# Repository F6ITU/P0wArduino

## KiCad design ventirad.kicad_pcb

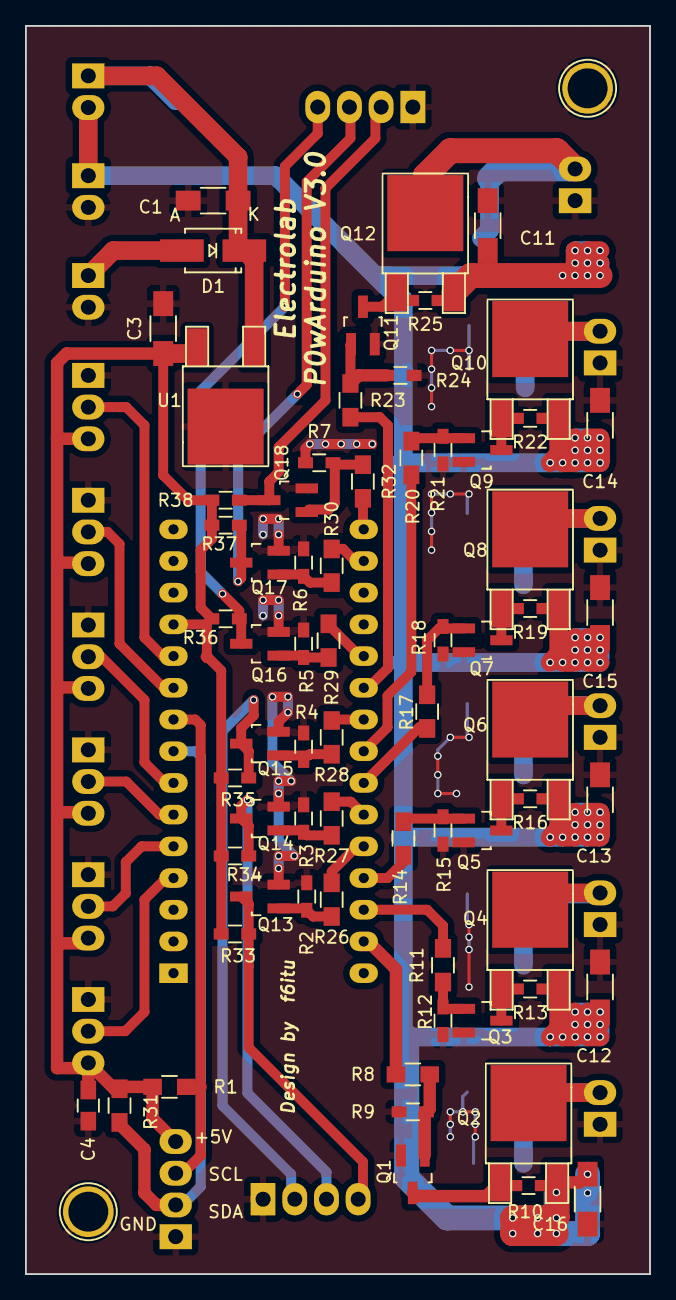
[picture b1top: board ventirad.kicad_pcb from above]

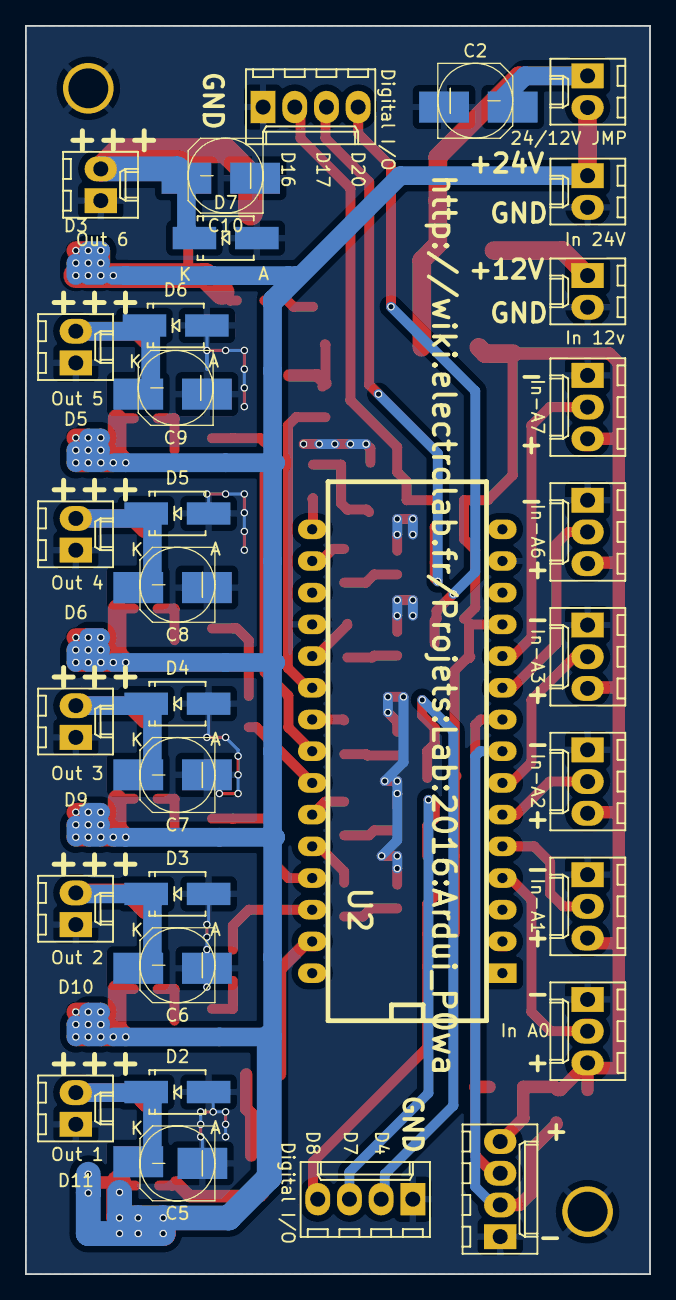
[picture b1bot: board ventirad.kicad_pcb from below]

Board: 2 copper layers, 50.0 x 100.0 mm, 81 parts (14 on the bottom side), 48 nets.

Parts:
C1, C3, C11, C12, C13, C14, C15, C16: 100n; C_1206_HandSoldering
C2: 200u; c_elec_6.3x7.7
C4: 10n; C_0805_HandSoldering
C5, C6, C7, C8, C9, C10: 100u; c_elec_6.3x7.7
D1, D2, D3, D4, D5, D6, D7: SS-26; SMA_Handsoldering
Q1, Q3, Q5, Q7, Q9, Q11, Q13, Q14, Q15, Q16, Q17, Q18: 2N7000; SOT-23_Handsoldering
Q2, Q4, Q6, Q8, Q10, Q12: IRFR9014; TO-252-2Lead
R1, R31: 10k; R_0805_HandSoldering
R2, R3, R4, R5, R6, R7, R9, R10, R12, R13, R15, R16, R18, R19, R21, R22, R24, R25, R33, R34, R35, R36, R37, R38: 10k; R_0603_HandSoldering
R8, R11, R14, R17, R20, R23, R26, R27, R28, R29, R30, R32: 1k; R_0805_HandSoldering
U1: LM7805; TO-252-2Lead
U2: http://wiki.electrolab.fr/Projets:Lab:2016:Ardui_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; arduino_nano

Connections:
+5V: C3.1, C4.1, R1.2, R31.2, R33.1, R34.1, R35.1, R36.1, R37.1, R38.1, U1.3, U2.12
+12V: C1.1, C2.1, D1.1, U1.1
GND: C1.2, C2.2, C3.2, C4.2, C5.2, C6.2, C7.2, C8.2, C9.2, C10.2, C11.1, C12.1, C13.1, C14.1, C15.1, C16.1, D2.2, D3.2, D4.2, D5.2, D6.2, D7.2, Q1.2, Q3.2, Q5.2, Q7.2, Q9.2, Q11.2, Q13.2, Q14.2, Q15.2, Q16.2, Q17.2, Q18.2, R2.2, R3.2, R4.2, R5.2, R6.2, R7.2, R9.2, R12.2, R15.2, R18.2, R21.2, R24.2, U1.2, U2.14, U2.19
unnamed: C5.1, D2.1, Q2.2
unnamed: C6.1, D3.1, Q4.2
unnamed: C7.1, D4.1, Q6.2
unnamed: C8.1, D5.1, Q8.2
unnamed: C9.1, D6.1, Q10.2
unnamed: C10.1, D7.1, Q12.2
unnamed: C11.2, C12.2, C13.2, C14.2, C15.2, C16.2, Q2.3, Q4.3, Q6.3, Q8.3, Q10.3, Q12.3, R10.1, R13.1, R16.1, R19.1, R22.1, R25.1
unnamed: R31.1, U2.8
unnamed: R1.1, U2.9
unnamed: Q15.3, R35.2
unnamed: Q14.3, R34.2
unnamed: Q13.3, R33.2
unnamed: Q18.3, R38.2
unnamed: Q17.3, R37.2
unnamed: Q16.3, R36.2
unnamed: Q1.1, R8.1, R9.1
unnamed: Q1.3, Q2.1, R10.2
unnamed: Q3.1, R11.1, R12.1
unnamed: Q3.3, Q4.1, R13.2
unnamed: Q5.1, R14.1, R15.1
unnamed: Q5.3, Q6.1, R16.2
unnamed: Q7.1, R17.1, R18.1
unnamed: Q7.3, Q8.1, R19.2
unnamed: Q9.1, R20.1, R21.1
unnamed: Q9.3, Q10.1, R22.2
unnamed: Q11.1, R23.1, R24.1
unnamed: Q11.3, Q12.1, R25.2
unnamed: Q13.1, R2.1, R26.1
unnamed: Q14.1, R3.1, R27.1
unnamed: Q15.1, R4.1, R28.1
unnamed: Q16.1, R5.1, R29.1
unnamed: Q17.1, R6.1, R30.1
unnamed: Q18.1, R7.1, R32.1
unnamed: R8.2, U2.29
unnamed: R11.2, U2.28
unnamed: R14.2, U2.27
unnamed: R17.2, U2.24
unnamed: R20.2, U2.23
unnamed: R23.2, U2.21
unnamed: R26.2, U2.26
unnamed: R27.2, U2.25
unnamed: R28.2, U2.22
unnamed: R29.2, U2.20
unnamed: R30.2, U2.17
unnamed: R32.2, U2.16

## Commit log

2016-05-02 Projet Ventirad, projet initial
2017-05-02 version Shielded et empreinte capapol elargies
2018-09-02 lib cleaning, mounting holes
2018-09-02 cleaning rm files
2019-03-15 upgrade to Kicad 5.x
2024-01-02 some file refresh and ibom, kicad 7 files
